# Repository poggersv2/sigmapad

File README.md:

# Sigmapad

Sigmapad is a 9-key macropad in a 3x3 grid with an EC11 rotary encoder. It runs on QMK firmware. 

It was built as part of Hack Club's Stardance and Hackpad programs to handle frequently used shortcuts and keys.

## Features
- 9 Keys in a standard 3x3 grid.
- EC11 Rotary encoder (with built-in push switch) for whatever you want.
- USB-C connectivity.

## CAD Model
The case consists of three printed parts: the top frame, the switch plate, and the bottom enclosure. 
Everything fits together using four M3x16mm screws and M3 heat-set inserts.

## PCB
Here's the schematic and board layout. 

## Firmware 
This macropad uses [QMK](https://qmk.fm/) firmware. 
The rotary encoder changes volume and mutes on press. 
The default keys are:

```text
┌───┬───┬───┐
│ Q │ W │ E │
├───┼───┼───┤
│ A │ S │ D │
├───┼───┼───┤
│ Z │ X │ C │
└───┴───┴───┘
```

To flash the board, compile your `.uf2` file, hold the BOOT button on the RP2040 while plugging it in, and drag the file onto the mounted drive. 

## BOM
Here is everything you need to build this macropad:

- 1x Seeed Studio XIAO RP2040
- 9x Cherry MX-style Switches
- 9x White Blank DSA Keycaps
- 9x Through-hole 1N4148 Diodes
- 1x EC11 Rotary Encoder
- 4x M3x16mm Screws
- 4x M3x5x4mm Heat-set Inserts
- 1x Case (Top, Plate, Bottom)

## Extra stuff
**Tools I used:**
* **CAD:** Fusion
* **PCB and Schematic:** KiCad

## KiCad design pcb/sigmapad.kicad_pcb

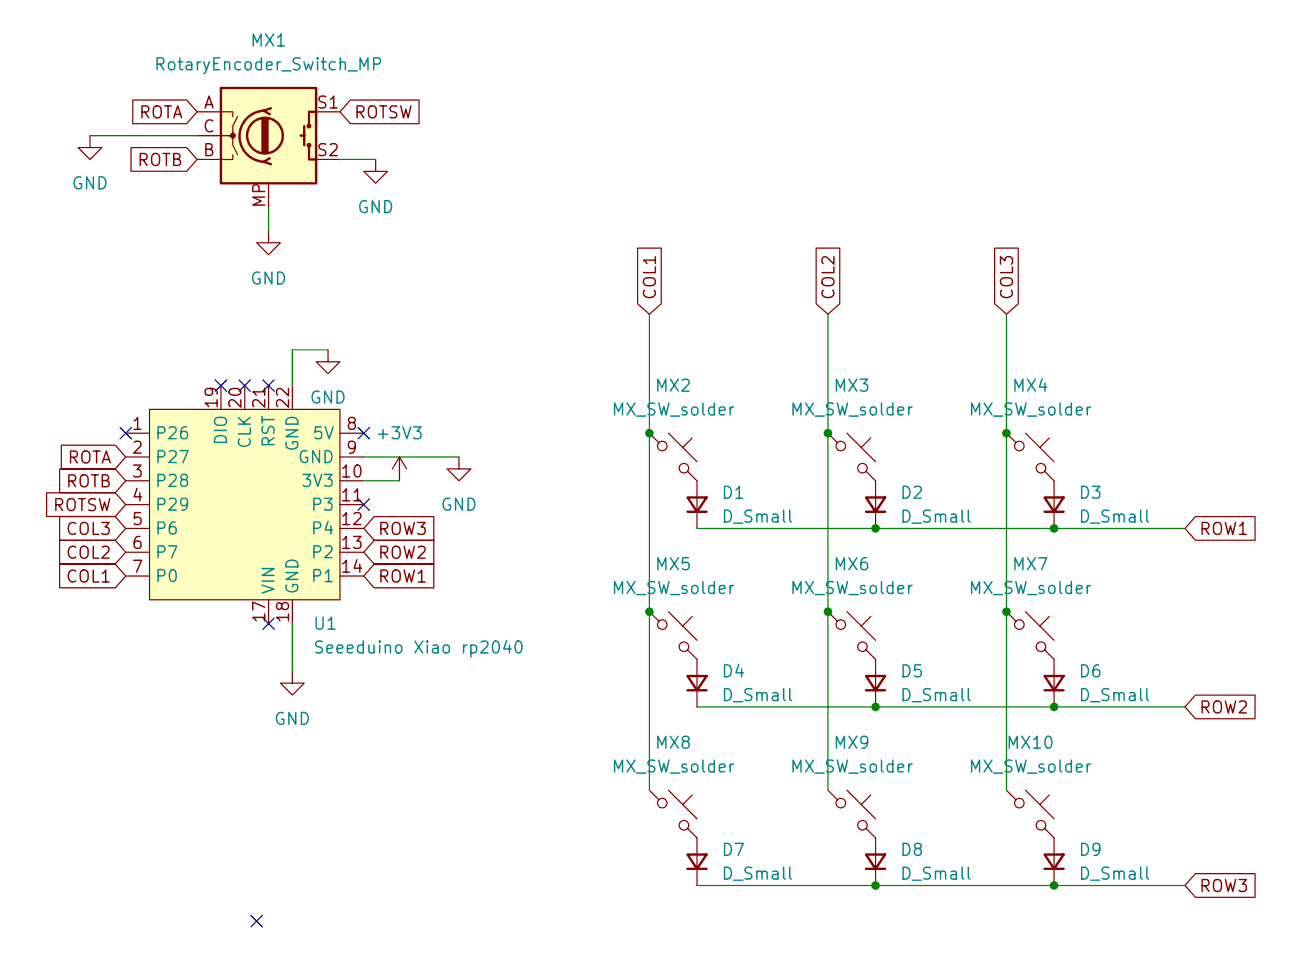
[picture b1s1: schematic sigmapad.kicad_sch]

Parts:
D1, D2, D3, D4, D5, D6, D7, D8, D9: D_Small; D_DO-35_SOD27_P7.62mm_Horizontal
MX1: RotaryEncoder_Switch_MP; ROT_Alps_EC11E-Switch
MX2, MX3, MX4, MX5, MX6, MX7, MX8, MX9, MX10: MX_SW_solder; SW_MX_1u
U1: Seeeduino Xiao rp2040; Xiao_rp2040_ACH

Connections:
+3V3: U1.10 (3V3)
COL1: MX2.1, MX5.1, MX8.1, U1.7 (P0)
COL2: MX3.1, MX6.1, MX9.1, U1.6 (P7)
COL3: MX4.1, MX7.1, MX10.1, U1.5 (P6)
GND: MX1.C, MX1.MP, MX1.S2, U1.9 (GND), U1.18 (GND), U1.22 (GND)
unnamed: D1.2 (A), MX2.2
unnamed: D2.2 (A), MX3.2
unnamed: D3.2 (A), MX4.2
unnamed: D4.2 (A), MX5.2
unnamed: D5.2 (A), MX6.2
unnamed: D6.2 (A), MX7.2
unnamed: D7.2 (A), MX8.2
unnamed: D8.2 (A), MX9.2
unnamed: D9.2 (A), MX10.2
ROTA: MX1.A, U1.2 (P27)
ROTB: MX1.B, U1.3 (P28)
ROTSW: MX1.S1, U1.4 (P29)
ROW1: D1.1 (K), D2.1 (K), D3.1 (K), U1.14 (P1)
ROW2: D4.1 (K), D5.1 (K), D6.1 (K), U1.13 (P2)
ROW3: D7.1 (K), D8.1 (K), D9.1 (K), U1.12 (P4)

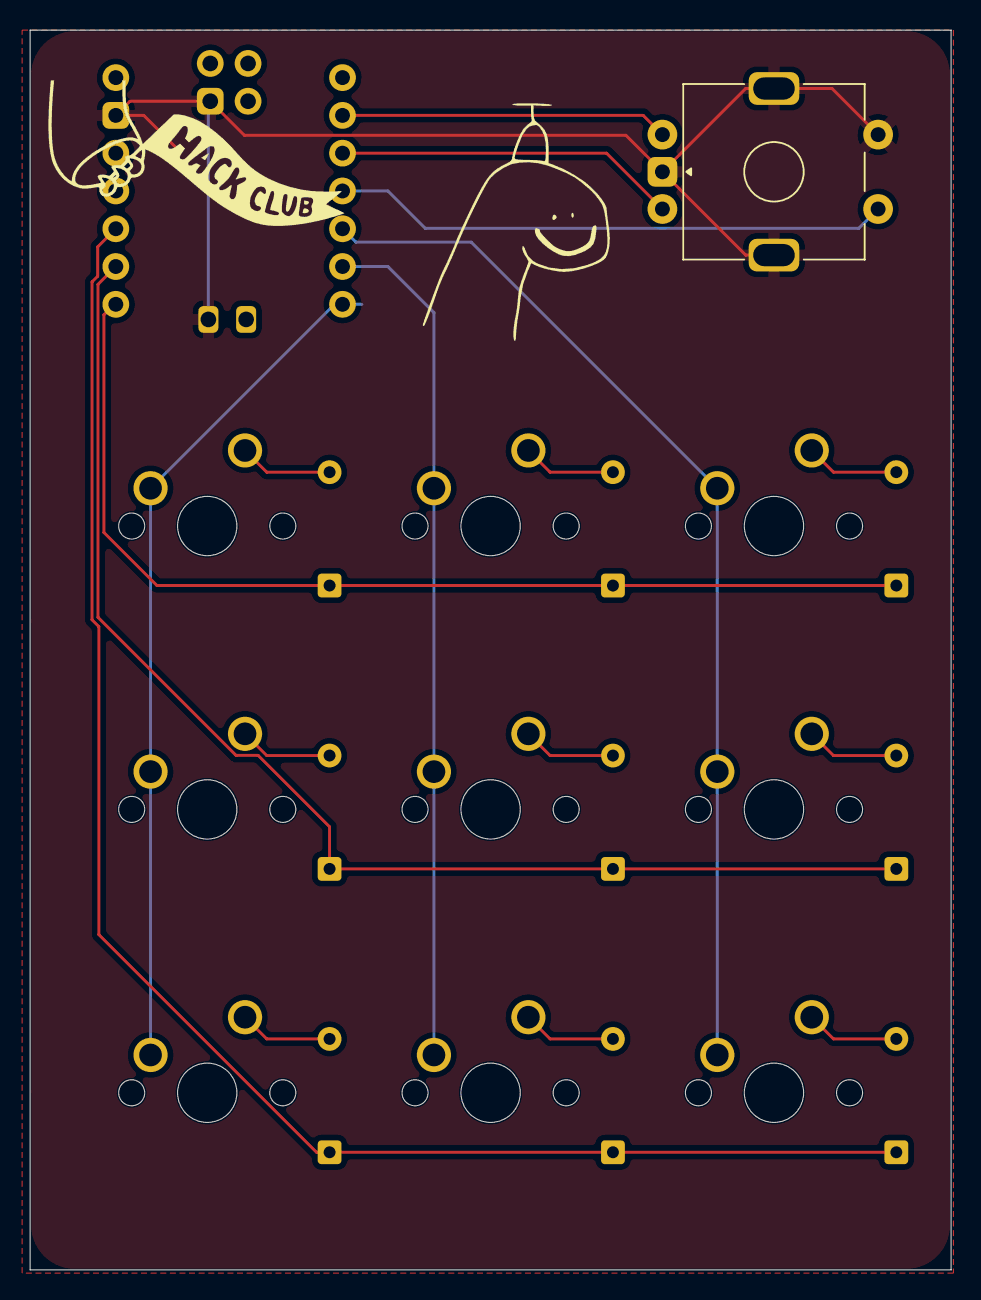
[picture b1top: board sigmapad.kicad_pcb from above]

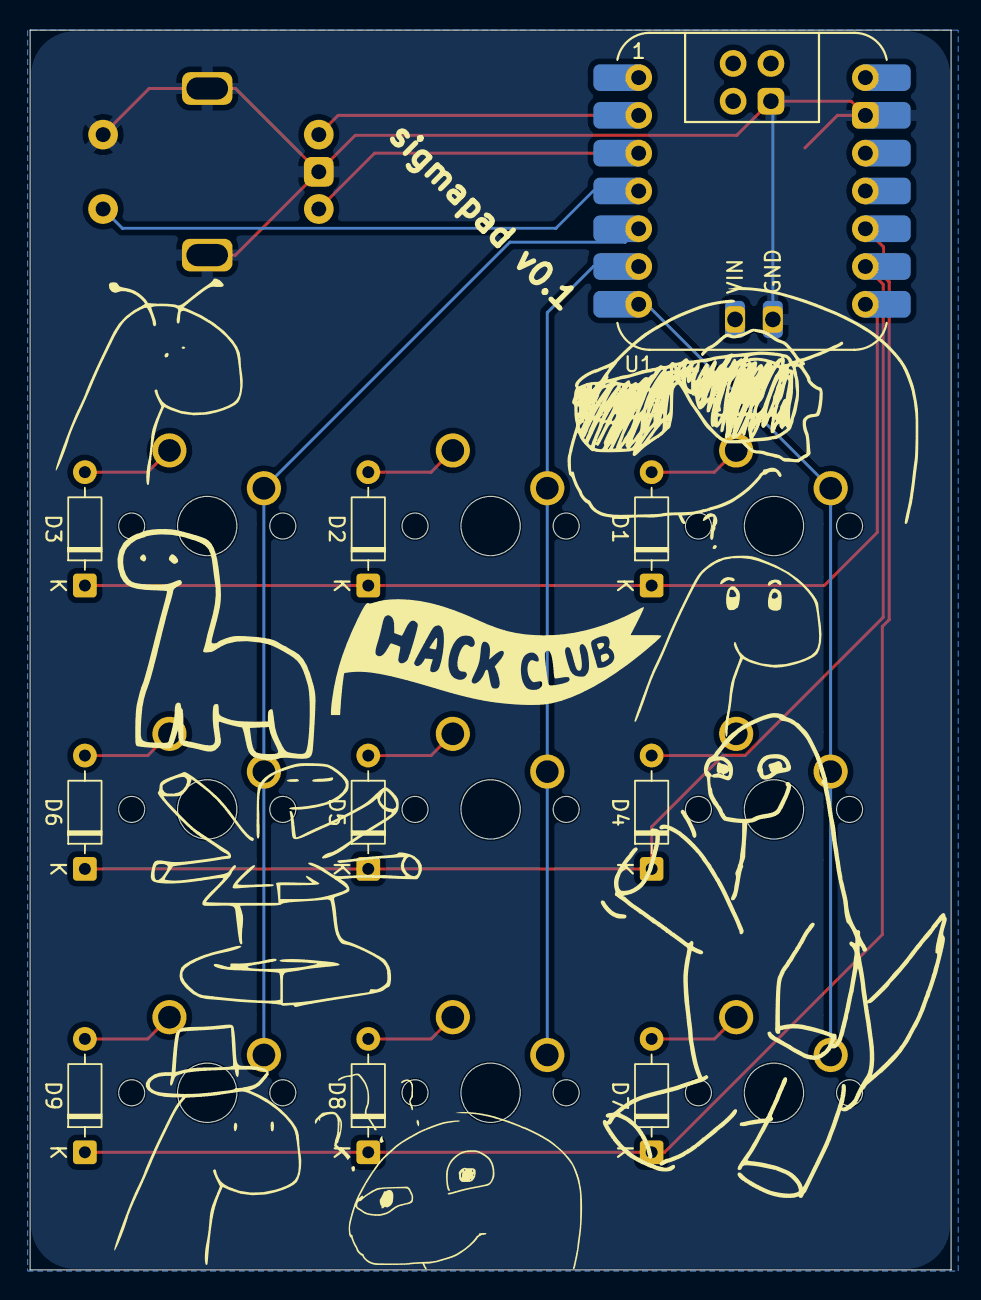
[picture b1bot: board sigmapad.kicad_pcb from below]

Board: 2 copper layers, 61.9 x 83.3 mm, 20 parts (10 on the bottom side), 19 nets.

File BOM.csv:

"Reference","Qty","Value","DNP","Exclude from BOM","Exclude from Board","Footprint","Datasheet"
"D1,D2,D3,D4,D5,D6,D7,D8,D9","9","D_Small","","","","Diode_THT:D_DO-35_SOD27_P7.62mm_Horizontal",""
"MX1","1","RotaryEncoder_Switch_MP","","","","PCM_marbastlib-various:ROT_Alps_EC11E-Switch",""
"MX2,MX3,MX4,MX5,MX6,MX7,MX8,MX9,MX10","9","MX_SW_solder","","","","PCM_marbastlib-mx:SW_MX_1u",""
